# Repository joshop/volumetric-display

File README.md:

# Volumetric Display Board
This is the KiCAD EDA files for a Persistence of Vision-based volumetric display based on the Zero Tiny BLE model by Zero Engineering (zeroengineering.io). It uses the following components:
* ATTiny85 for processing and control
* a 9x16 LED array from Adafruit (not included in CAD) for the visual output
* HM-10 bluetooth radio for relaying to/from the device
* a 3.7V rechargeable LiPo battery for power

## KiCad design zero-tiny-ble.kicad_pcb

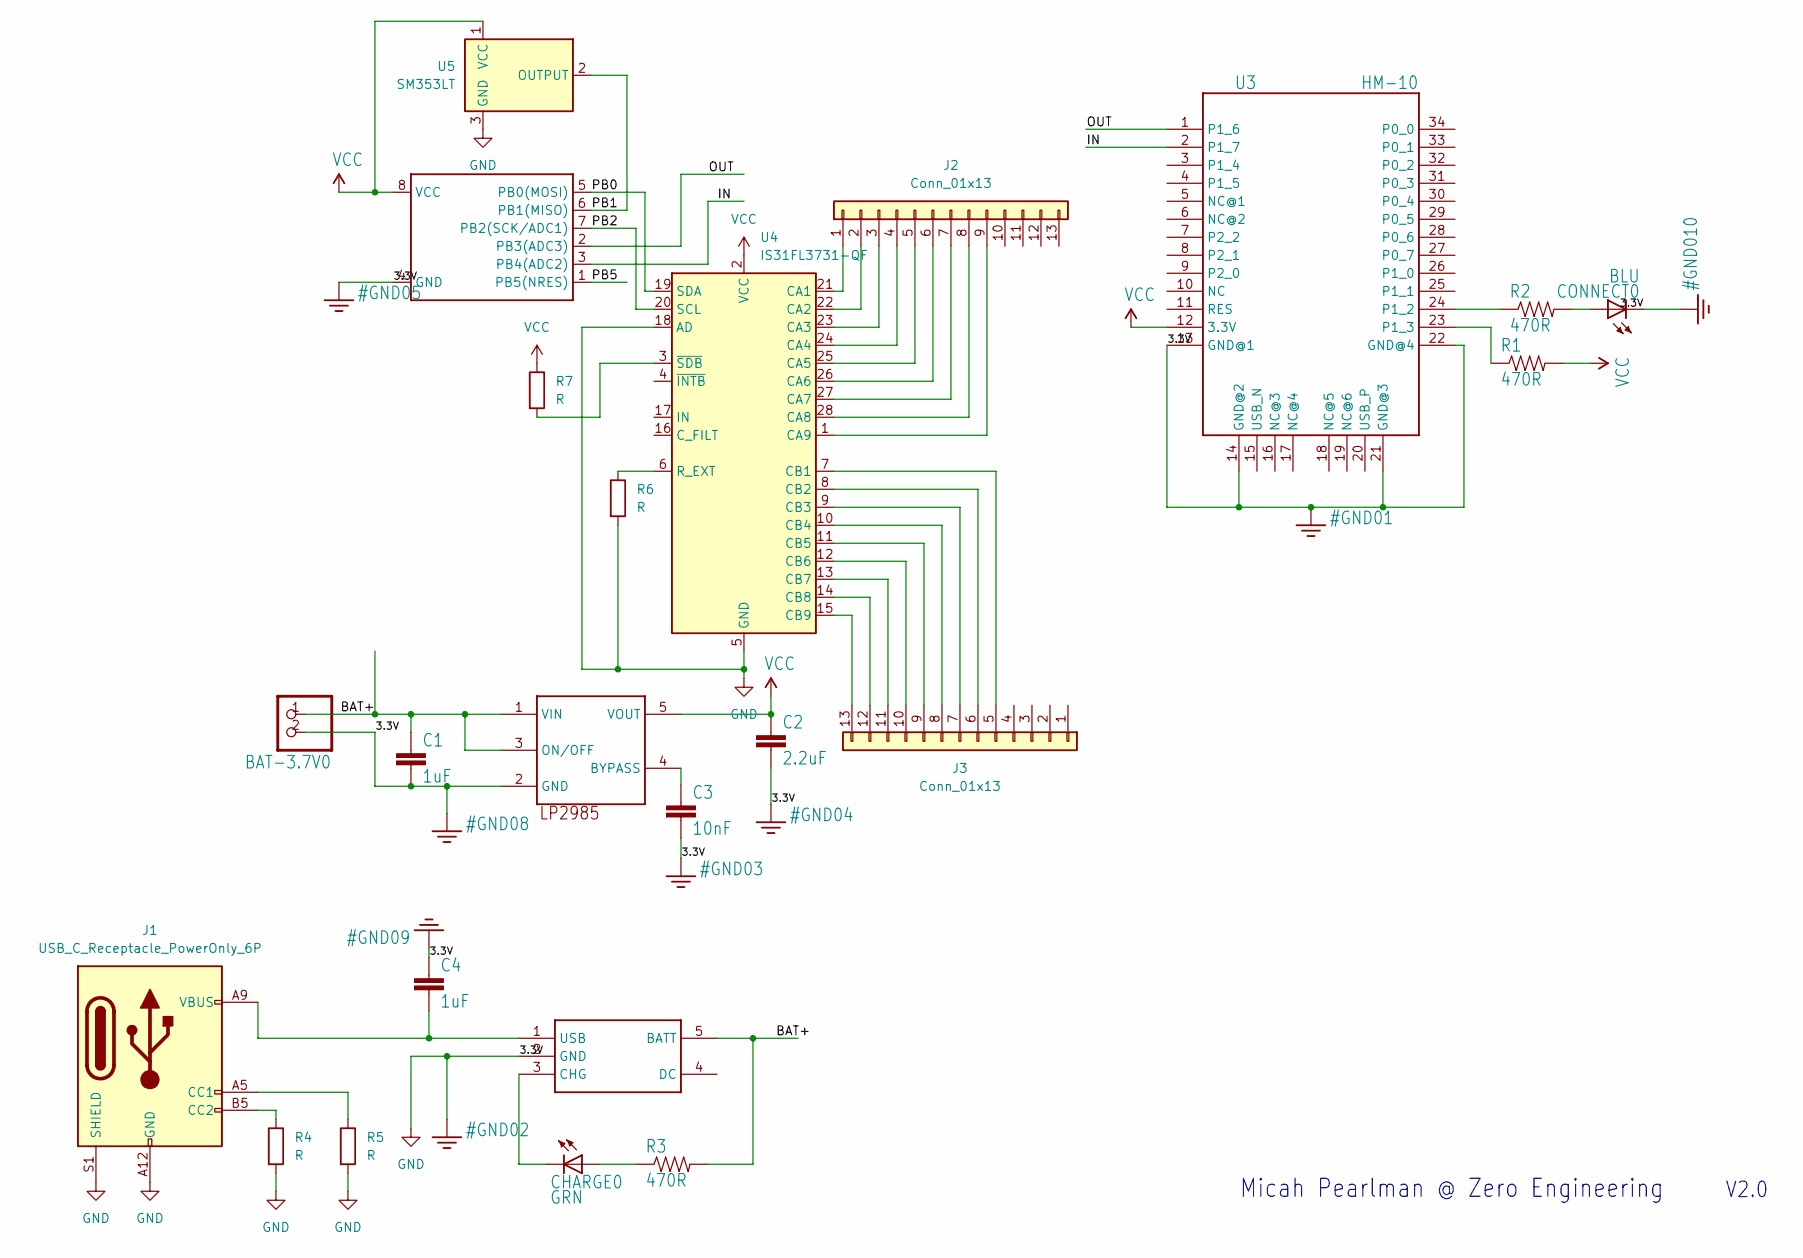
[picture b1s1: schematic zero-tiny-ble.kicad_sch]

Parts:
BAT-3.7V0: JST_2PIN-THM; JST-PH-2-THM
C1, C4: 1uF; 0805
C2: 2.2uF; 0805
C3: 10nF; 0805
CHARGE0: GRN; CHIPLED_0805
CONNECT0: BLU; CHIPLED_0805
J1: USB_C_Receptacle_PowerOnly_6P; USB_C_Receptacle_GCT_USB4135-GF-A_6P_TopMnt_Horizontal
J2, J3: Conn_01x13; PinHeader_1x13_P2.54mm_Vertical
R1, R2, R3: 470R; 0805
R4, R5, R6, R7: R; R_0805_2012Metric
U1: MAX1555; SOT23-5
U2: attiny85; DIP08
U3: HM-10
U4: IS31FL3731-QF; QFN-28-1EP_4x4mm_P0.4mm_EP2.3x2.3mm
U5: SM353LT; SOT-23
U$2: LP2985AIM5-3.3; SOT25

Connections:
3.3V: BAT-3.7V0.2 (1), C1.2, C2.2, C3.2, C4.1, CONNECT0.C, J1.A12 (GND), J1.B12 (GND), J1.S1 (SHIELD), R4.2, R5.2, R6.2, U1.2 (GND), U2.4 (GND), U3.13 (GND@1), U3.14 (GND@2), U3.21 (GND@3), U3.22 (GND@4), U4.5 (GND), U4.18 (AD), U4.29 (GND), U5.3 (GND), U$2.2 (GND)
/BAT+: BAT-3.7V0.1 (2), C1.1, R3.2, U1.5 (BATT), U$2.1 (VIN), U$2.3 (ON/OFF)
/IN: U2.3 (PB4(ADC2)), U3.2 (P1_7)
/OUT: U2.2 (PB3(ADC3)), U3.1 (P1_6)
/PB0: U2.5 (PB0(MOSI)), U4.19 (SDA)
/PB1: U2.6 (PB1(MISO)), U5.2 (OUTPUT)
/PB2: U2.7 (PB2(SCK/ADC1)), U4.20 (SCL)
/PB5: U2.1 (PB5(NRES))
unnamed: CHARGE0.A, R3.1
unnamed: CONNECT0.A, R2.2
unnamed: J1.A5 (CC1), R5.1
unnamed: J1.B5 (CC2), R4.1
unnamed: J2.1, U4.21 (CA1)
unnamed: J2.2, U4.22 (CA2)
unnamed: J2.3, U4.23 (CA3)
unnamed: J2.4, U4.24 (CA4)
unnamed: J2.5, U4.25 (CA5)
unnamed: J2.6, U4.26 (CA6)
unnamed: J2.7, U4.27 (CA7)
unnamed: J2.8, U4.28 (CA8)
unnamed: J2.9, U4.1 (CA9)
unnamed: J3.5, U4.7 (CB1)
unnamed: J3.6, U4.8 (CB2)
unnamed: J3.7, U4.9 (CB3)
unnamed: J3.8, U4.10 (CB4)
unnamed: J3.9, U4.11 (CB5)
unnamed: J3.10, U4.12 (CB6)
unnamed: J3.11, U4.13 (CB7)
unnamed: J3.12, U4.14 (CB8)
unnamed: J3.13, U4.15 (CB9)
unnamed: CHARGE0.C, U1.3 (CHG)
unnamed: C4.2, J1.A9 (VBUS), J1.B9 (VBUS), U1.1 (USB)
unnamed: R2.1, U3.24 (P1_2)
unnamed: R1.1, U3.23 (P1_3)
unnamed: R6.1, U4.6 (R_EXT)
unnamed: R7.2, U4.3 (~SDB)
unnamed: C3.1, U$2.4 (BYPASS)
VCC: C2.1, R1.2, R7.1, U2.8 (VCC), U3.12 (3.3V), U4.2 (VCC), U5.1 (VCC), U$2.5 (VOUT)

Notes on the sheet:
Micah Pearlman @ Zero Engineering
V2.0

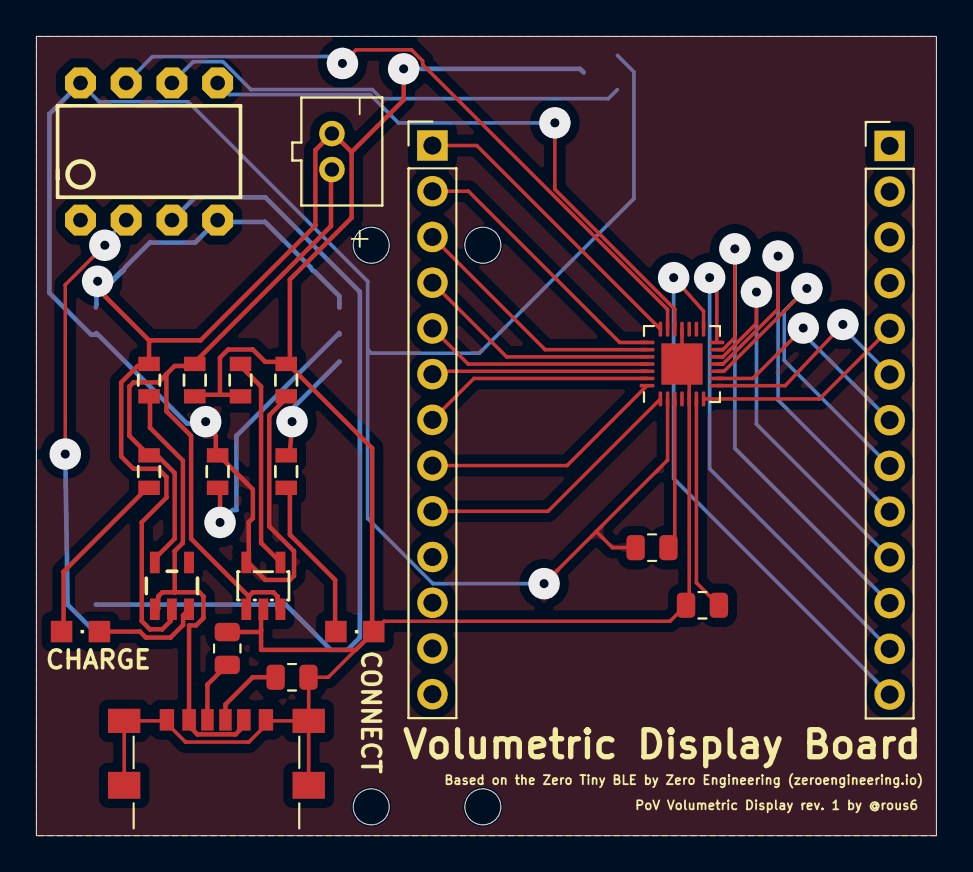
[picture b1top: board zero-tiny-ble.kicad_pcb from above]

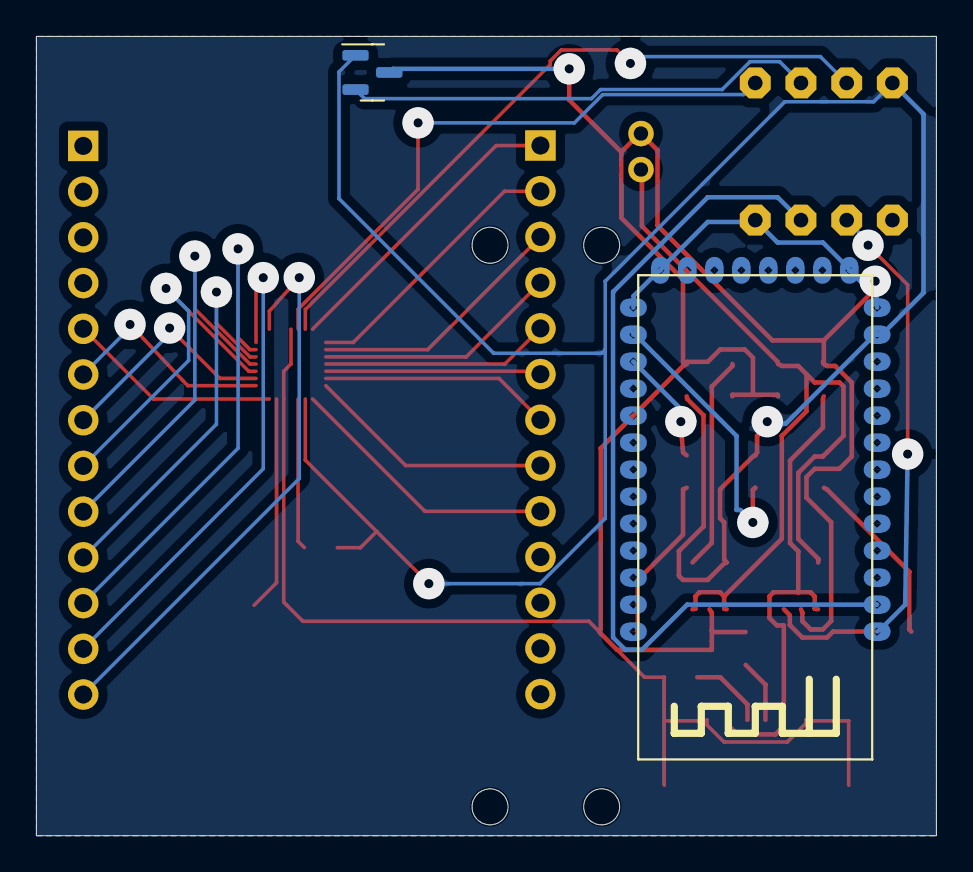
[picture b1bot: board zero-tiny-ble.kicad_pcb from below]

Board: 2 copper layers, 50.0 x 44.4 mm, 23 parts (2 on the bottom side), 37 nets.
